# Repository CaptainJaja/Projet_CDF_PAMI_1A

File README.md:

# 🤖 Projet Coupe de France de Robotique 2025 – Design PCB 4 couches et Code STM32

Bienvenue sur le dépôt dédié à mon **design de PCB 4 couches** réalisé dans le cadre de la **Coupe de France de Robotique 2025** organisée par Planète Sciences.  
👉 [Site officiel](https://www.coupederobotique.fr/)

Je participe à cette aventure en tant qu'étudiant de **première année à l'ENSEA**, au sein de l'association **ARES Robotique**, avec une équipe composée également de deuxièmes années.

---

## 🧩 Description du PCB

Ce PCB a été conçu pour les **PAMI** (*Petits Actionneurs Mobiles Indépendants*), et intègre les fonctionnalités suivantes :

- 🧠 **Microcontrôleur :** STM32 L552CCT6
- ⚙️ **Driver moteur :** TB6612FNG
- 🚗 **2 connecteurs pour moteurs DC N20**
- 🔁 **2 connecteurs pour servomoteurs**
- 🧭 **1 connecteur pour module ultrason** (détection et évitement d'obstacles)
- ⚫ **1 connecteur pour module suiveur de ligne infrarouge 4 voies**
- 🔘 **Bouton reset**
- 🔌 **Pins GPIO, 3.3V, GND**
- 🔋 **Connecteur alimentation 7.4V (batterie Ni-Mh)**
- 🔧 **2 régulateurs DC-DC** (5V et 3.3V)
- 🔁 **Bobines, condensateurs, résistances**
- 🛠️ **Connecteur ST-Link** pour programmation et debug

---

## 🎬 Démos en GIF

### 🔩 PCB assemblé avec les composants soudés

### 🚗 Suiveur de ligne en action

---

## 🖼️ Vues des 4 couches du PCB

| Couche | Image |
|--------|-------|
| **Face avant (Front)** |  |
| **Plan de masse (In1)** |  |
| **Plan d'alimentation (In2)** |  |
| **Face arrière (Back)** |  |

---

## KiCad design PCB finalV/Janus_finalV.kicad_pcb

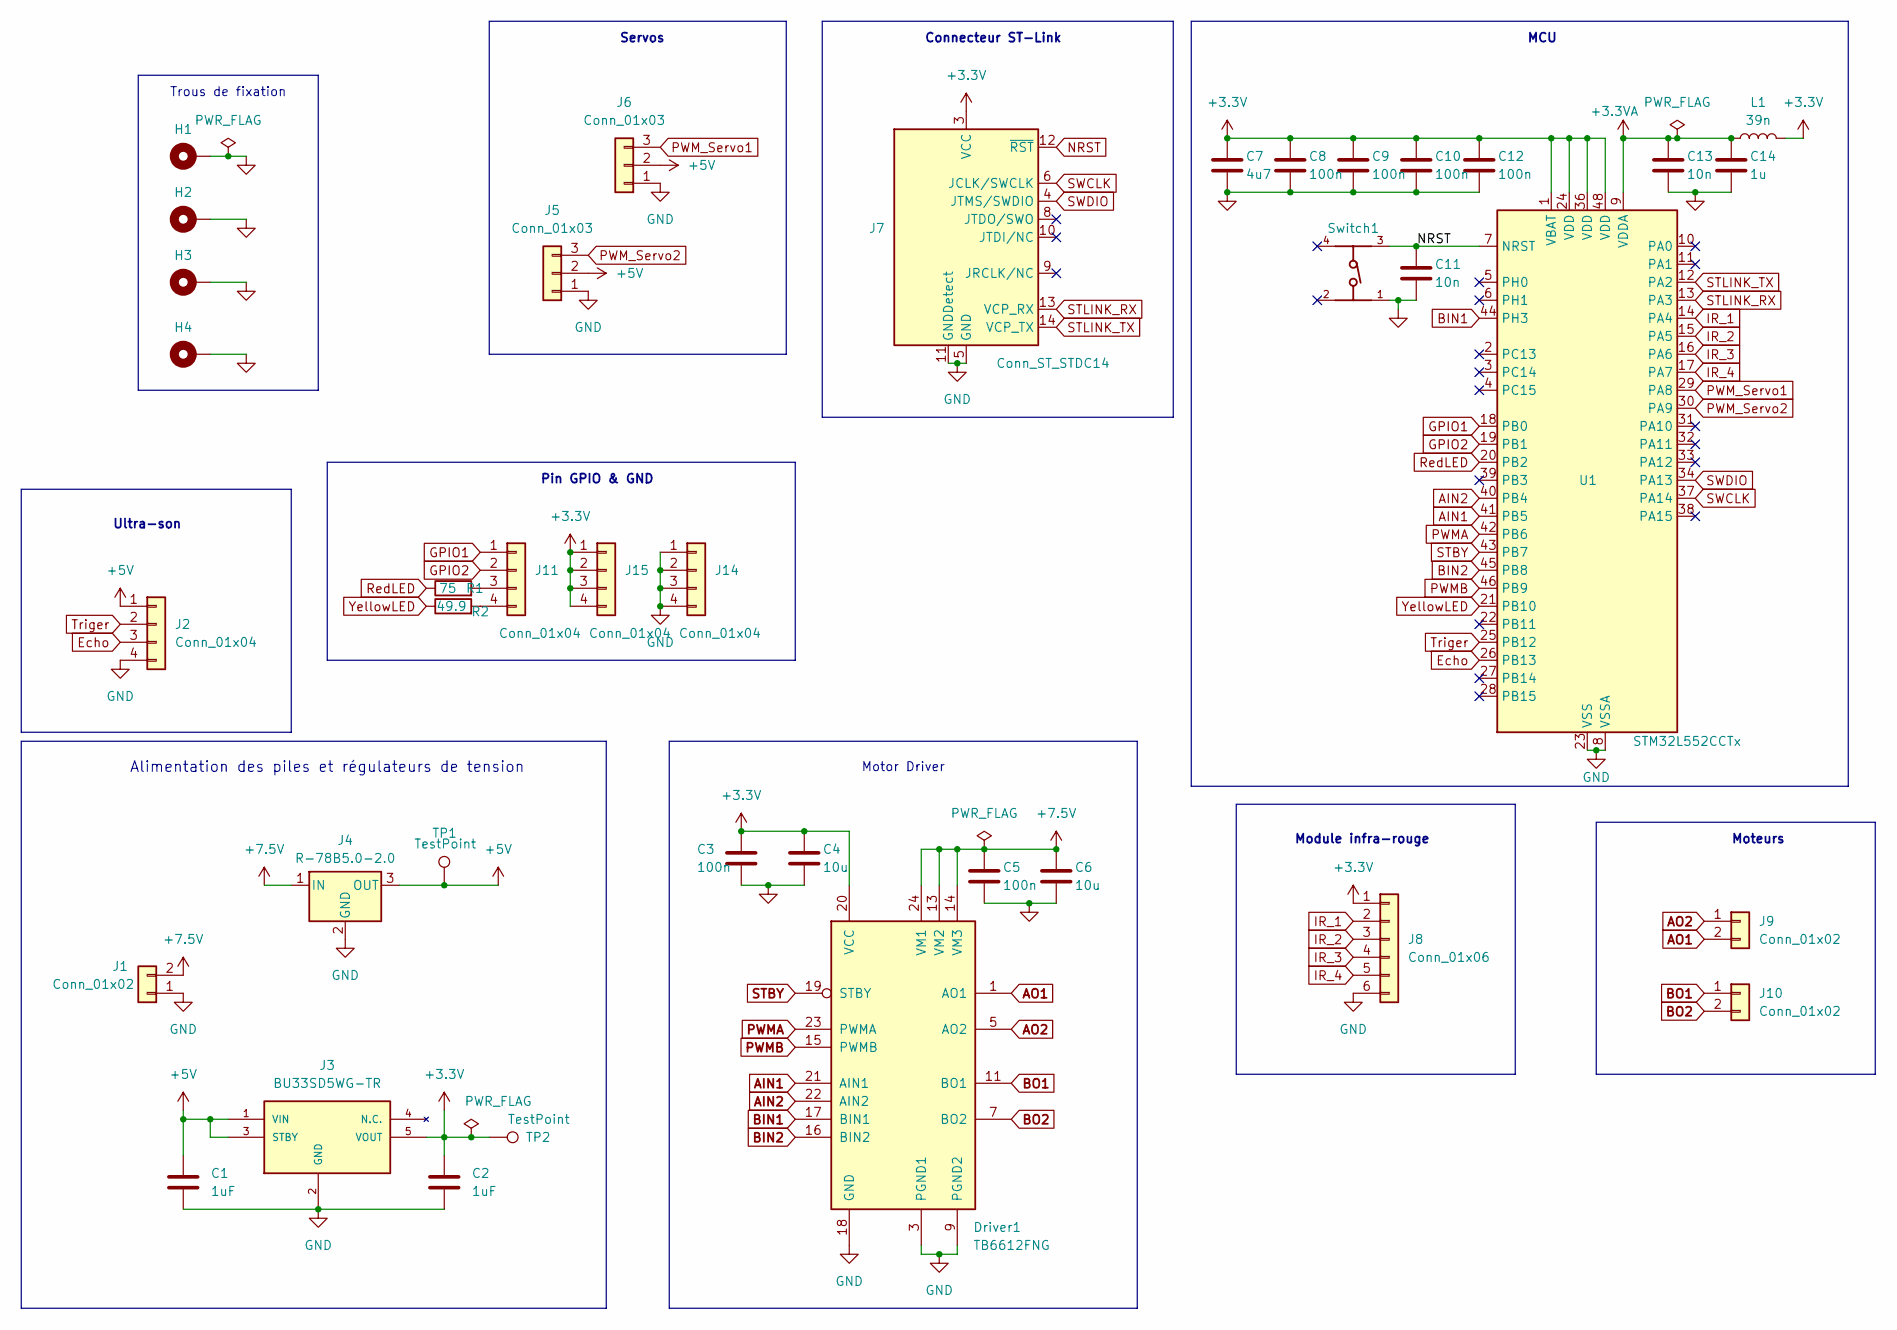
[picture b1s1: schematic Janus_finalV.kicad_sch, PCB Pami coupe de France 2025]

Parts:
C1, C2: 1uF; C_0603_1608Metric_Pad1.08x0.95mm_HandSolder
C3, C5, C8, C9, C10, C12: 100n; C_0402_1005Metric
C4, C6: 10u; C_0805_2012Metric
C7: 4u7; C_0805_2012Metric
C11, C13: 10n; C_0402_1005Metric
C14: 1u; C_0402_1005Metric
Driver1: TB6612FNG; SSOP-24_5.3x8.2mm_P0.65mm
H1, H2, H3, H4: MountingHole_Pad; MountingHole_2.7mm_M2.5_Pad
J1: Conn_01x02; JST_XH_S2B-XH-A-1_1x02_P2.50mm_Horizontal
J2: Conn_01x04; JST_PH_B4B-PH-K_1x04_P2.00mm_Vertical
J3: BU33SD5WG-TR; SOT95P280X125-5N; Mouser_Part_Number 755-BU33SD5WG-TR
J4: R-78B5.0-2.0; Converter_DCDC_RECOM_R-78B-2.0_THT
J5, J6: Conn_01x03; JST_XH_B3B-XH-A_1x03_P2.50mm_Vertical
J7: Conn_ST_STDC14; PinHeader_2x07_P1.27mm_Vertical_SMD
J8: Conn_01x06; JST_XH_S6B-XH-A-1_1x06_P2.50mm_Horizontal
J9, J10: Conn_01x02; JST_XH_B2B-XH-A_1x02_P2.50mm_Vertical
J11, J14, J15: Conn_01x04; PinHeader_1x04_P2.54mm_Vertical
L1: 39n; L_0603_1608Metric
R1: 75; R_0402_1005Metric_Pad0.72x0.64mm_HandSolder
R2: 49.9; R_0402_1005Metric_Pad0.72x0.64mm_HandSolder
Switch1: 430471025826; PART-NUMBER 430471025826
TP1, TP2: TestPoint; TestPoint_Pad_D2.0mm
U1: STM32L552CCTx; LQFP-48_7x7mm_P0.5mm

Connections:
+3.3V: C2.1, C3.1, C4.1, C7.1, C8.1, C9.1, C10.1, C12.1, Driver1.20 (VCC), J3.5 (VOUT), J7.3 (VCC), J8.1, J15.1, J15.2, J15.3, J15.4, L1.2, TP2.1, U1.1 (VBAT), U1.24 (VDD), U1.36 (VDD), U1.48 (VDD)
+3.3VA: C13.1, C14.1, L1.1, U1.9 (VDDA)
+5V: C1.1, J2.1, J3.1 (VIN), J3.3 (STBY), J4.3 (OUT), J5.2, J6.2, TP1.1
+7.5V: C5.1, C6.1, Driver1.13 (VM2), Driver1.14 (VM3), Driver1.24 (VM1), J1.2, J4.1 (IN)
AIN1: Driver1.21 (AIN1), U1.41 (PB5)
AIN2: Driver1.22 (AIN2), U1.40 (PB4)
AO1: Driver1.1 (AO1), Driver1.2 (AO1), J9.2
AO2: Driver1.5 (AO2), Driver1.6 (AO2), J9.1
BIN1: Driver1.17 (BIN1), U1.44 (PH3)
BIN2: Driver1.16 (BIN2), U1.45 (PB8)
BO1: Driver1.11 (BO1), Driver1.12 (BO1), J10.1
BO2: Driver1.7 (BO2), Driver1.8 (BO2), J10.2
Echo: J2.3, U1.26 (PB13)
GND: C1.2, C2.2, C3.2, C4.2, C5.2, C6.2, C7.2, C8.2, C9.2, C10.2, C11.2, C12.2, C13.2, C14.2, Driver1.3 (PGND1), Driver1.4 (PGND1), Driver1.9 (PGND2), Driver1.10 (PGND2), Driver1.18 (GND), H1.1, H2.1, H3.1, H4.1, J1.1, J2.4, J3.2 (GND), J4.2 (GND), J5.1, J6.1, J7.5 (GND), J7.7 (GND), J7.11 (GNDDetect), J8.6, J14.1, J14.2, J14.3, J14.4, Switch1.1, U1.8 (VSSA), U1.23 (VSS), U1.35 (VSS), U1.47 (VSS)
GPIO1: J11.1, U1.18 (PB0)
GPIO2: J11.2, U1.19 (PB1)
IR_1: J8.2, U1.14 (PA4)
IR_2: J8.3, U1.15 (PA5)
IR_3: J8.4, U1.16 (PA6)
IR_4: J8.5, U1.17 (PA7)
NRST: C11.1, J7.12 (~RST), Switch1.3, U1.7 (NRST)
unnamed: J11.3, R1.2
unnamed: J11.4, R2.2
PWMA: Driver1.23 (PWMA), U1.42 (PB6)
PWMB: Driver1.15 (PWMB), U1.46 (PB9)
PWM_Servo1: J6.3, U1.29 (PA8)
PWM_Servo2: J5.3, U1.30 (PA9)
RedLED: R1.1, U1.20 (PB2)
STBY: Driver1.19 (STBY), U1.43 (PB7)
STLINK_RX: J7.13 (VCP_RX), U1.13 (PA3)
STLINK_TX: J7.14 (VCP_TX), U1.12 (PA2)
SWCLK: J7.6 (JCLK/SWCLK), U1.37 (PA14)
SWDIO: J7.4 (JTMS/SWDIO), U1.34 (PA13)
Triger: J2.2, U1.25 (PB12)
YellowLED: R2.1, U1.21 (PB10)

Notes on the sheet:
Trous de fixation
Servos
Moteurs
Module infra-rouge
Connecteur ST-Link
Ultra-son
Alimentation des piles et régulateurs de tension
Motor Driver
Pin GPIO & GND
MCU

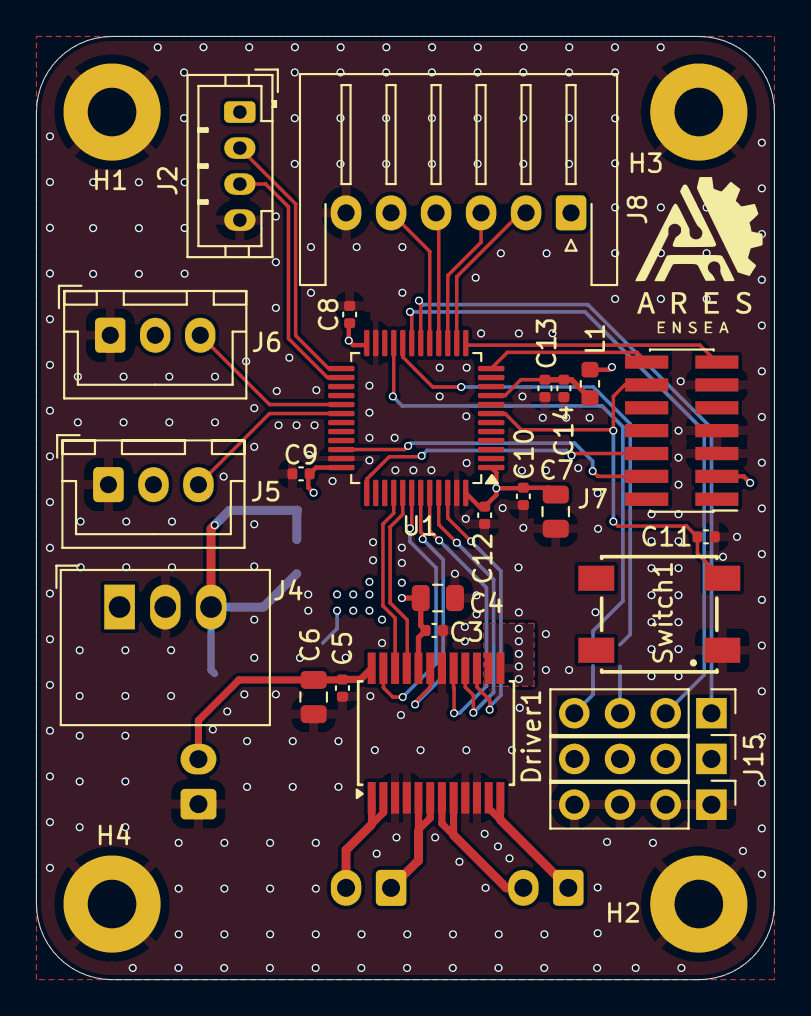
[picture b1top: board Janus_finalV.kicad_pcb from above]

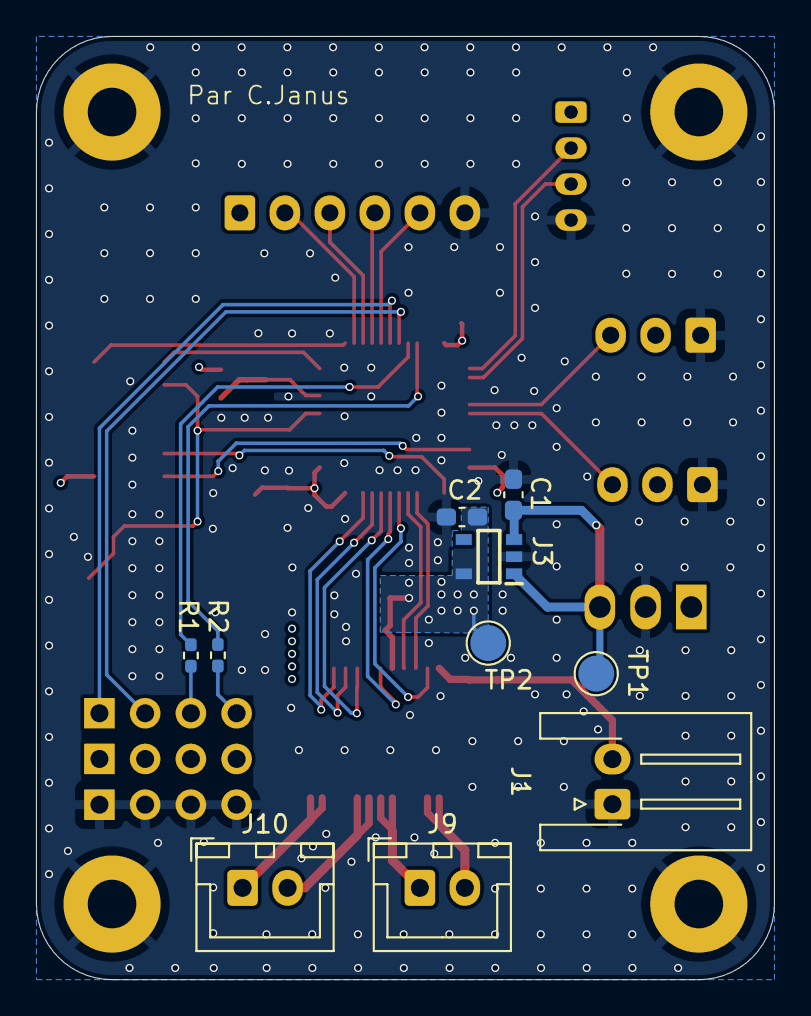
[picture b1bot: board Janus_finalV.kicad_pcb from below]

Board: 4 copper layers, 41.0 x 52.4 mm, 39 parts (10 on the bottom side), 35 nets.

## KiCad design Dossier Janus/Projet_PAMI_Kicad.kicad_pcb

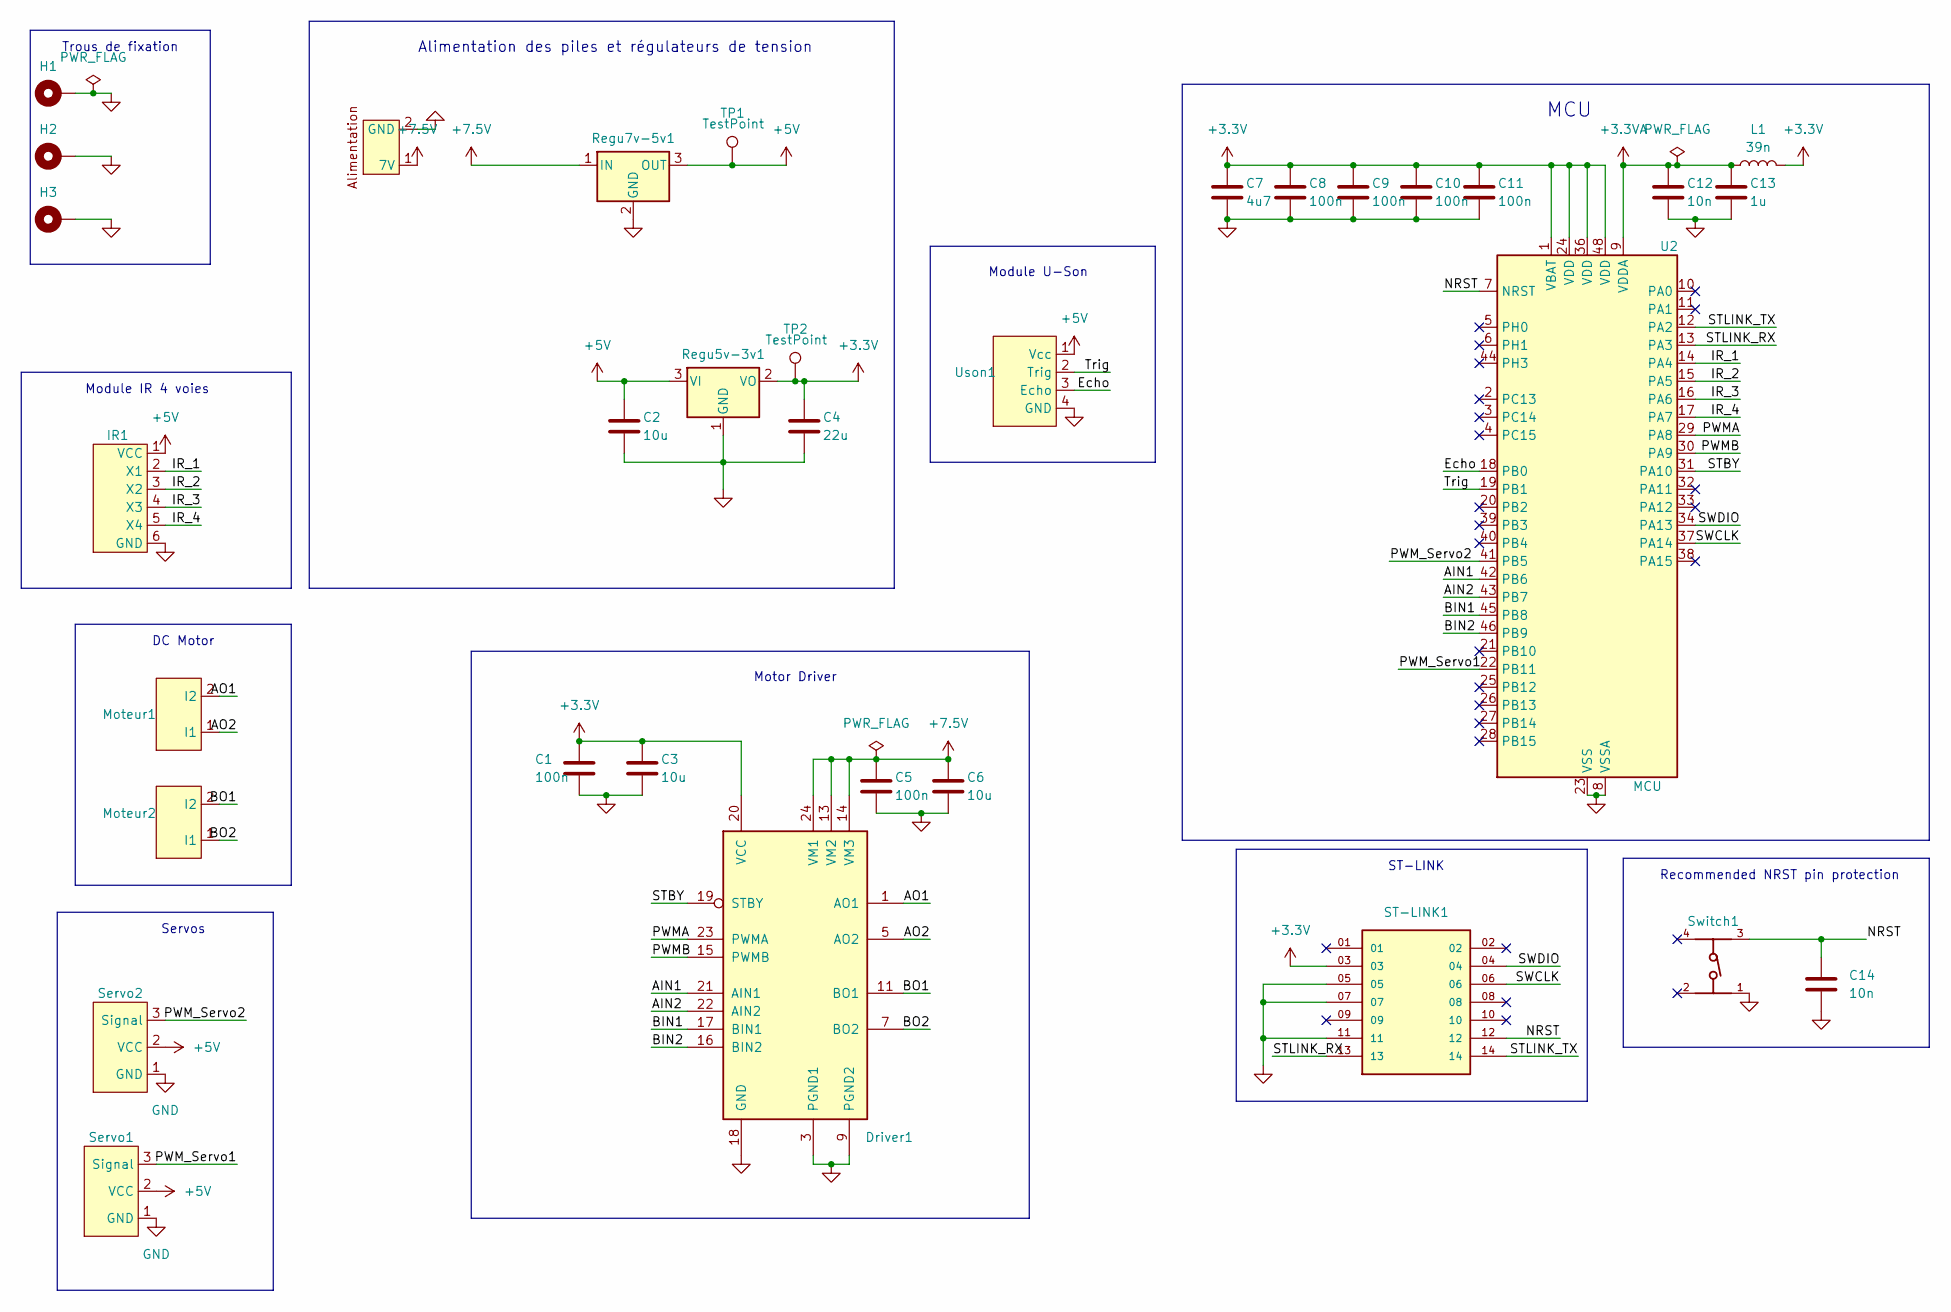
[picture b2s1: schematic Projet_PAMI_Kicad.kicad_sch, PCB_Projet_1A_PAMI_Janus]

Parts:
C1, C5, C8, C9, C10, C11: 100n; C_0402_1005Metric
C2, C3, C6: 10u; C_0805_2012Metric
C4: 22u; C_0805_2012Metric
C7: 4u7; C_0805_2012Metric
C12, C14: 10n; C_0402_1005Metric
C13: 1u; C_0402_1005Metric
Driver1: TB6612FNG; SSOP-24_5.3x8.2mm_P0.65mm
H1, H2, H3: MountingHole_Pad; MountingHole_2.7mm_M2.5_Pad
IR1: JST_XH_S6B-XH-A-1_1x06_P2.50mm_Horizontal
L1: 39n; L_0603_1608Metric
Moteur1, Moteur2: JST_XH_B2B-XH-A_1x02_P2.50mm_Vertical
Regu5v-3v1: AZ1117-3.3; SOT-223-3_TabPin2
Regu7v-5v1: R-78B5.0-2.0; Converter_DCDC_RECOM_R-78B-2.0_THT
ST-LINK1: FTSH-107-01-F-DV-K; SAMTEC_FTSH-107-01-F-DV-K; PARTREV R
Servo1, Servo2: JST_PH_B3B-PH-K_1x03_P2.00mm_Vertical
Switch1: 430471025826; PART-NUMBER 430471025826
TP1, TP2: TestPoint; TestPoint_Pad_D2.0mm
U1: JST_PH_B2B-PH-K_1x02_P2.00mm_Vertical
U2: MCU; LQFP-48_7x7mm_P0.5mm
Uson1: JST_PH_B4B-PH-K_1x04_P2.00mm_Vertical

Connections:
+3.3V: C1.1, C3.1, C4.1, C7.1, C8.1, C9.1, C10.1, C11.1, Driver1.20 (VCC), L1.2, Regu5v-3v1.2 (VO), ST-LINK1.03, TP2.1, U2.1 (VBAT), U2.24 (VDD), U2.36 (VDD), U2.48 (VDD)
+3.3VA: C12.1, C13.1, L1.1, U2.9 (VDDA)
+5V: C2.1, IR1.1 (VCC), Regu5v-3v1.3 (VI), Regu7v-5v1.3 (OUT), Servo1.2 (VCC), Servo2.2 (VCC), TP1.1, Uson1.1 (Vcc)
+7.5V: C5.1, C6.1, Driver1.13 (VM2), Driver1.14 (VM3), Driver1.24 (VM1), Regu7v-5v1.1 (IN), U1.1 (7V)
/AIN1: Driver1.21 (AIN1), U2.42 (PB6)
/AIN2: Driver1.22 (AIN2), U2.43 (PB7)
/AO1: Driver1.1 (AO1), Driver1.2 (AO1), Moteur1.2 (I2)
/AO2: Driver1.5 (AO2), Driver1.6 (AO2), Moteur1.1 (I1)
/BIN1: Driver1.17 (BIN1), U2.45 (PB8)
/BIN2: Driver1.16 (BIN2), U2.46 (PB9)
/BO1: Driver1.11 (BO1), Driver1.12 (BO1), Moteur2.2 (I2)
/BO2: Driver1.7 (BO2), Driver1.8 (BO2), Moteur2.1 (I1)
/Echo: U2.18 (PB0), Uson1.3 (Echo)
/IR_1: IR1.2 (X1), U2.14 (PA4)
/IR_2: IR1.3 (X2), U2.15 (PA5)
/IR_3: IR1.4 (X3), U2.16 (PA6)
/IR_4: IR1.5 (X4), U2.17 (PA7)
/NRST: C14.1, ST-LINK1.12, Switch1.3, U2.7 (NRST)
/PWMA: Driver1.23 (PWMA), U2.29 (PA8)
/PWMB: Driver1.15 (PWMB), U2.30 (PA9)
/PWM_Servo1: Servo1.3 (Signal), U2.22 (PB11)
/PWM_Servo2: Servo2.3 (Signal), U2.41 (PB5)
/STBY: Driver1.19 (STBY), U2.31 (PA10)
/STLINK_RX: ST-LINK1.13, U2.13 (PA3)
/STLINK_TX: ST-LINK1.14, U2.12 (PA2)
/SWCLK: ST-LINK1.06, U2.37 (PA14)
/SWDIO: ST-LINK1.04, U2.34 (PA13)
/Trig: U2.19 (PB1), Uson1.2 (Trig)
GND: C1.2, C2.2, C3.2, C4.2, C5.2, C6.2, C7.2, C8.2, C9.2, C10.2, C11.2, C12.2, C13.2, C14.2, Driver1.3 (PGND1), Driver1.4 (PGND1), Driver1.9 (PGND2), Driver1.10 (PGND2), Driver1.18 (GND), H1.1, H2.1, H3.1, IR1.6 (GND), Regu5v-3v1.1 (GND), Regu7v-5v1.2 (GND), ST-LINK1.05, ST-LINK1.07, ST-LINK1.11, Servo1.1 (GND), Servo2.1 (GND), Switch1.1, U1.2 (GND), U2.8 (VSSA), U2.23 (VSS), U2.35 (VSS), U2.47 (VSS), Uson1.4 (GND)

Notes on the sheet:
Trous de fixation
Motor Driver
DC Motor
Module U-Son
Alimentation des piles et régulateurs de tension
Recommended NRST pin protection
Module IR 4 voies
MCU
Servos
ST-LINK

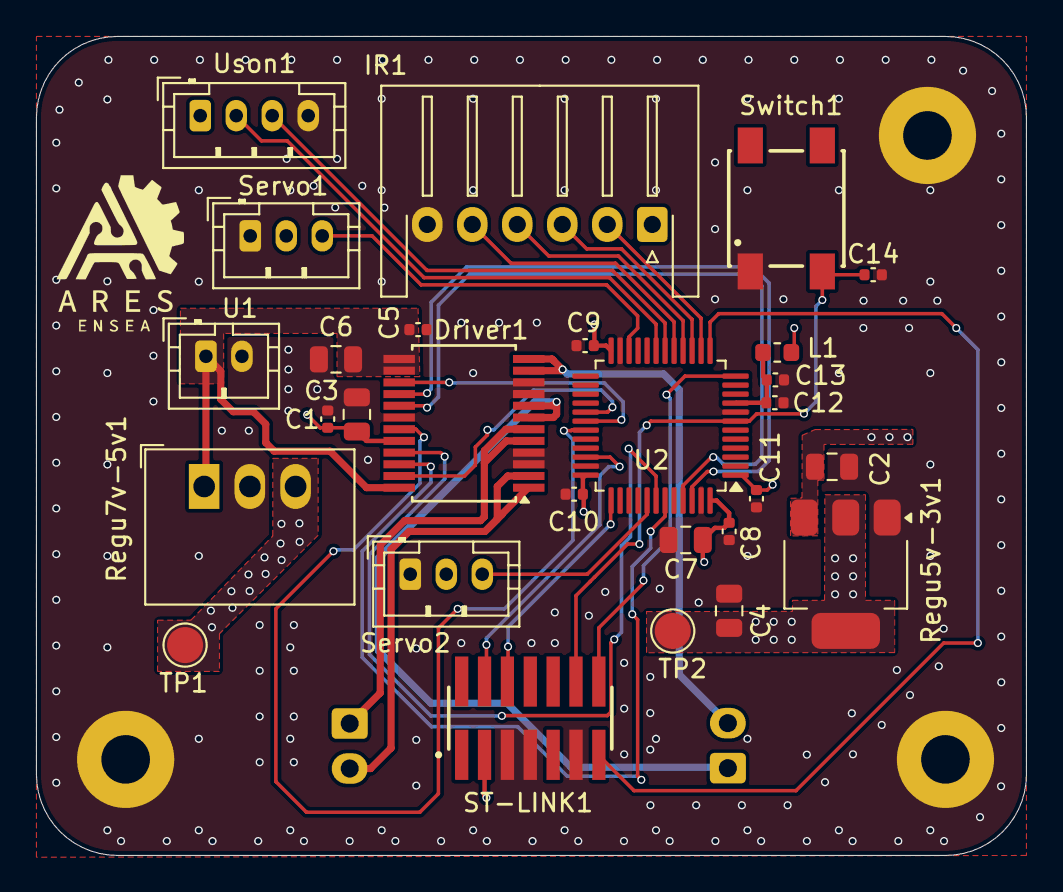
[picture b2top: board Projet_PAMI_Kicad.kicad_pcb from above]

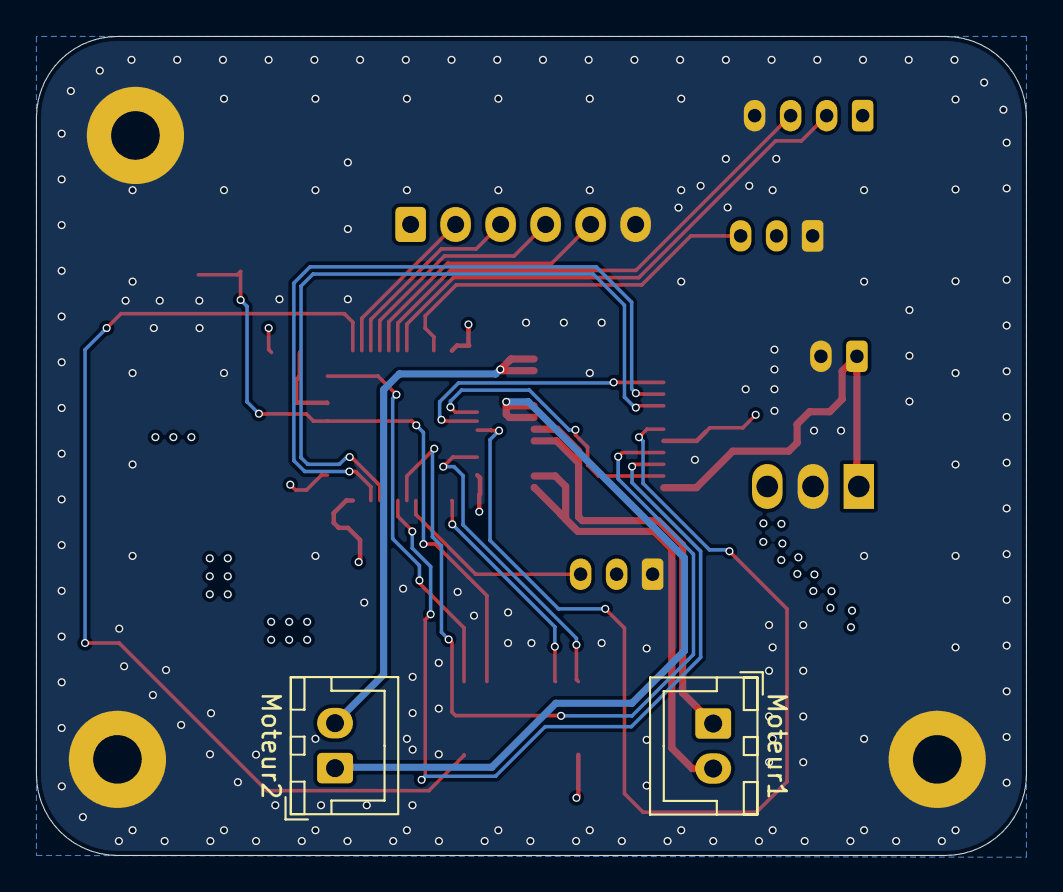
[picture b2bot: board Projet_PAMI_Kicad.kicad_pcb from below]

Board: 4 copper layers, 55.0 x 45.5 mm, 33 parts (2 on the bottom side), 29 nets.

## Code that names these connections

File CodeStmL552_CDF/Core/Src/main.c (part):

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ADC_ChannelConfTypeDef sConfig;
void HAL_GPIO_EXTI_Rising_Callback(uint16_t GPIO_Pin)
{
    if (GPIO_Pin == ECHO_Pin) {
        timer_count = __HAL_TIM_GET_COUNTER(&htim1);
    }
    else if (GPIO_Pin ==Button_Pin){
    	STANBY=1-STANBY;
    	HAL_GPIO_WritePin(STBY_GPIO_Port, STBY_Pin, STANBY);

    }
}

void HAL_GPIO_EXTI_Falling_Callback(uint16_t GPIO_Pin)
{
    if (GPIO_Pin == ECHO_Pin) {
        current_count = __HAL_TIM_GET_COUNTER(&htim1);
        uint32_t delta;

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  MX_TIM4_Init();
  MX_ICACHE_Init();
  /* USER CODE BEGIN 2 */
  HAL_GPIO_WritePin(STBY_GPIO_Port, STBY_Pin, STANBY);
  // For the motors
  HAL_TIM_PWM_Start(&htim4, TIM_CHANNEL_1);
  HAL_TIM_PWM_Start(&htim4, TIM_CHANNEL_4);

  HAL_TIM_Base_Start(&htim1);
  HAL_GPIO_WritePin(TRIG_GPIO_Port, TRIG_Pin, GPIO_PIN_RESET); //pull the TRIG pin low
  HAL_ADCEx_Calibration_Start(&hadc1, ADC_SINGLE_ENDED); //for sensors calibration

  //Stop the motor
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  while (1)
  {
	  // Déclenche le capteur
	  	  HAL_GPIO_WritePin(TRIG_GPIO_Port, TRIG_Pin, GPIO_PIN_SET);
	  	  __HAL_TIM_SET_COUNTER(&htim1, 0);
	  	  while (__HAL_TIM_GET_COUNTER(&htim1) < 10); // 10 us
	  	  HAL_GPIO_WritePin(TRIG_GPIO_Port, TRIG_Pin, GPIO_PIN_RESET);


	  	if(Distance>8){
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  __HAL_RCC_GPIOB_CLK_ENABLE();

  /*Configure GPIO pin Output Level */
  HAL_GPIO_WritePin(GPIOB, TRIG_Pin|AIN2_Pin|AIN1_Pin|STBY_Pin
                          |BIN2_Pin, GPIO_PIN_RESET);

  /*Configure GPIO pin Output Level */
  HAL_GPIO_WritePin(BIN1_GPIO_Port, BIN1_Pin, GPIO_PIN_RESET);

  /*Configure GPIO pin : X1_Pin */
  GPIO_InitStruct.Pin = X1_Pin;
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  GPIO_InitStruct.Pull = GPIO_NOPULL;
  HAL_GPIO_Init(Button_GPIO_Port, &GPIO_InitStruct);

  /*Configure GPIO pins : TRIG_Pin AIN2_Pin AIN1_Pin STBY_Pin
                           BIN2_Pin */
  GPIO_InitStruct.Pin = TRIG_Pin|AIN2_Pin|AIN1_Pin|STBY_Pin
                          |BIN2_Pin;
  GPIO_InitStruct.Mode = GPIO_MODE_OUTPUT_PP;
  GPIO_InitStruct.Pull = GPIO_NOPULL;
  GPIO_InitStruct.Speed = GPIO_SPEED_FREQ_LOW;
  HAL_GPIO_Init(GPIOB, &GPIO_InitStruct);

  /*Configure GPIO pin : ECHO_Pin */
  GPIO_InitStruct.Pin = ECHO_Pin;
  GPIO_InitStruct.Mode = GPIO_MODE_IT_RISING_FALLING;
  GPIO_InitStruct.Pull = GPIO_NOPULL;
  HAL_GPIO_Init(ECHO_GPIO_Port, &GPIO_InitStruct);

  /*Configure GPIO pin : BIN1_Pin */
  GPIO_InitStruct.Pin = BIN1_Pin;
  GPIO_InitStruct.Mode = GPIO_MODE_OUTPUT_PP;
  GPIO_InitStruct.Pull = GPIO_NOPULL;
  GPIO_InitStruct.Speed = GPIO_SPEED_FREQ_LOW;
  HAL_GPIO_Init(BIN1_GPIO_Port, &GPIO_InitStruct);

  /* EXTI interrupt init*/
  HAL_NVIC_SetPriority(EXTI0_IRQn, 0, 0);
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
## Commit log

2025-01-18 premier commit, ajout de deux répertoires et modification README
2025-01-18 ajout des notes dans les dossiers
2025-01-18 Update Note Karim.txt
    pour explique les nouveau termes qu'on connait pas
2025-01-20 Ajout dans Note Janus les pins pour le STM32L552 en boîtier LQFP48
2025-01-20 Ajout des pins pour ST-Link dans note Janus
2025-01-20 ajout du Kicad dans Dossier Janus
2025-01-20 ajout dossier+modif Kicad
2025-01-21 Finalisation schematic + ressources
2025-01-21 correction des oublies de numérotation de pins
2025-01-22 Finalisation PCB
2025-01-22 Rectification
2025-01-23 Finalisation du PCB--Dossier Janus
2025-01-24 Mise à jour couche d'alimentation
2025-02-04 ajout du répertoire Dossier Janus-bis contenant la version finale du PCB
2025-02-05 Update final Version
2025-03-17 update PCB1A
2025-04-09 selection dossier final
2025-04-09 MAJ README
2025-04-09 modif nom dossier PCB
2025-04-09 ajout du code
2025-04-15 MAJ code PAMI
2025-06-12 update_final

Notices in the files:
CodeStmL552_CDF/Core/Src/main.c:
Copyright (c) 2025 STMicroelectronics.
All rights reserved.
This software is licensed under terms that can be found in the LICENSE file
